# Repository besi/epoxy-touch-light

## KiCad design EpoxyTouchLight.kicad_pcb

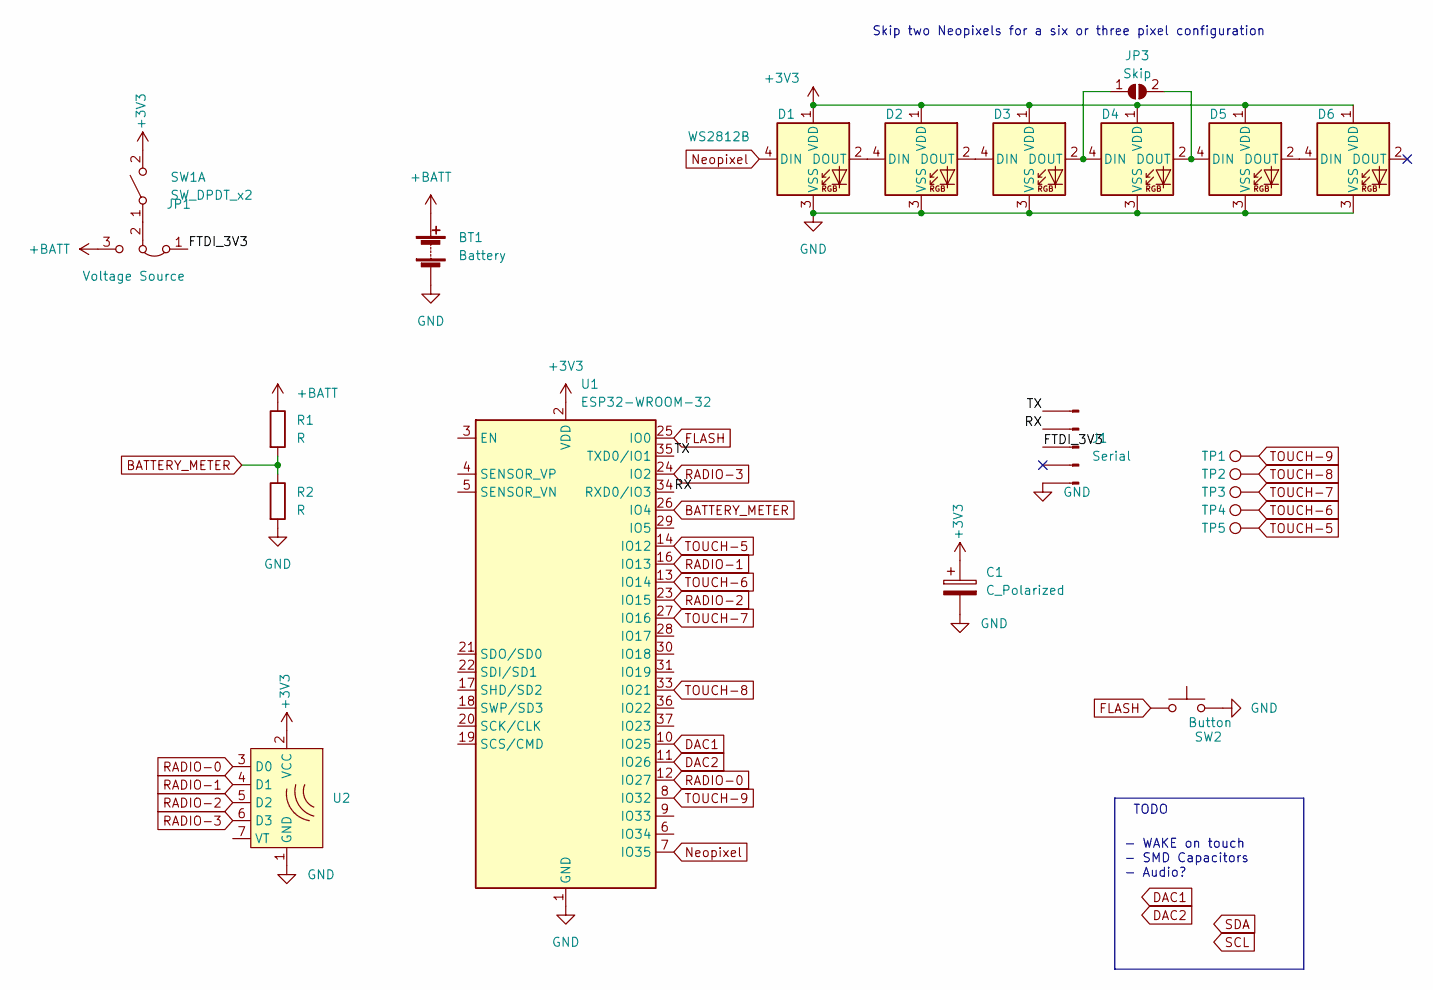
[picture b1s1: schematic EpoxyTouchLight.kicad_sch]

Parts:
BT1: Battery; BatteryHolder_Keystone_2479_3xAAA
C1: C_Polarized; CP_Radial_D5.0mm_P2.50mm
D1, D2, D3, D4, D5, D6: WS2812B; LED_WS2812B_PLCC4_5.0x5.0mm_P3.2mm
J1: Serial; PinHeader_1x05_P2.54mm_Horizontal
JP1: Voltage Source; PinHeader_1x03_P2.54mm_Horizontal
JP3: Skip; SolderJumper-2_P1.3mm_Open_TrianglePad1.0x1.5mm
R1, R2: R; R_Axial_DIN0207_L6.3mm_D2.5mm_P7.62mm_Horizontal
SW1: SW_DPDT_x2; SW_SPDT_CK-JS102011SAQN
SW2: Button; SW_PUSH_6mm_H4.3mm
TP1, TP2, TP3, TP4, TP5: Touch; TestPoint_Loop_D1.80mm_Drill1.0mm_Beaded
U1: ESP32-WROOM-32
U2: radio-receiver

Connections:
+3V3: C1.1, D1.1 (VDD), D2.1 (VDD), D3.1 (VDD), D4.1 (VDD), D5.1 (VDD), D6.1 (VDD), SW1.2 (B), U1.2 (VDD), U2.2 (VCC)
+BATT: BT1.1 (+), JP1.3 (B), R1.1
/FTDI_3V3: J1.3, JP1.1 (A)
/RX: J1.4, U1.34 (RXD0/IO3)
/TX: J1.5, U1.35 (TXD0/IO1)
BATTERY_METER: R1.2, R2.1, U1.26 (IO4)
DAC1: U1.10 (IO25)
DAC2: U1.11 (IO26)
FLASH: SW2.1, U1.25 (IO0)
GND: BT1.2 (-), C1.2, D1.3 (VSS), D2.3 (VSS), D3.3 (VSS), D4.3 (VSS), D5.3 (VSS), D6.3 (VSS), J1.1, R2.2, SW2.2, U1.1 (GND), U1.15 (GND), U1.38 (GND), U1.39 (GND), U2.1 (GND)
Neopixel: D1.4 (DIN), U1.7 (IO35)
unnamed: D1.2 (DOUT), D2.4 (DIN)
unnamed: D2.2 (DOUT), D3.4 (DIN)
unnamed: D3.2 (DOUT), D4.4 (DIN), JP3.1 (A)
unnamed: D4.2 (DOUT), D5.4 (DIN), JP3.2 (B)
unnamed: D5.2 (DOUT), D6.4 (DIN)
unnamed: JP1.2 (C), SW1.1 (A)
RADIO-0: U1.12 (IO27), U2.3 (D0)
RADIO-1: U1.16 (IO13), U2.4 (D1)
RADIO-2: U1.23 (IO15), U2.5 (D2)
RADIO-3: U1.24 (IO2), U2.6 (D3)
TOUCH-5: TP5.1, U1.14 (IO12)
TOUCH-6: TP4.1, U1.13 (IO14)
TOUCH-7: TP3.1, U1.27 (IO16)
TOUCH-8: TP2.1, U1.33 (IO21)
TOUCH-9: TP1.1, U1.8 (IO32)

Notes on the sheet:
Skip two Neopixels for a six or three pixel configuration
TODO
- WAKE on touch - SMD Capacitors - Audio?

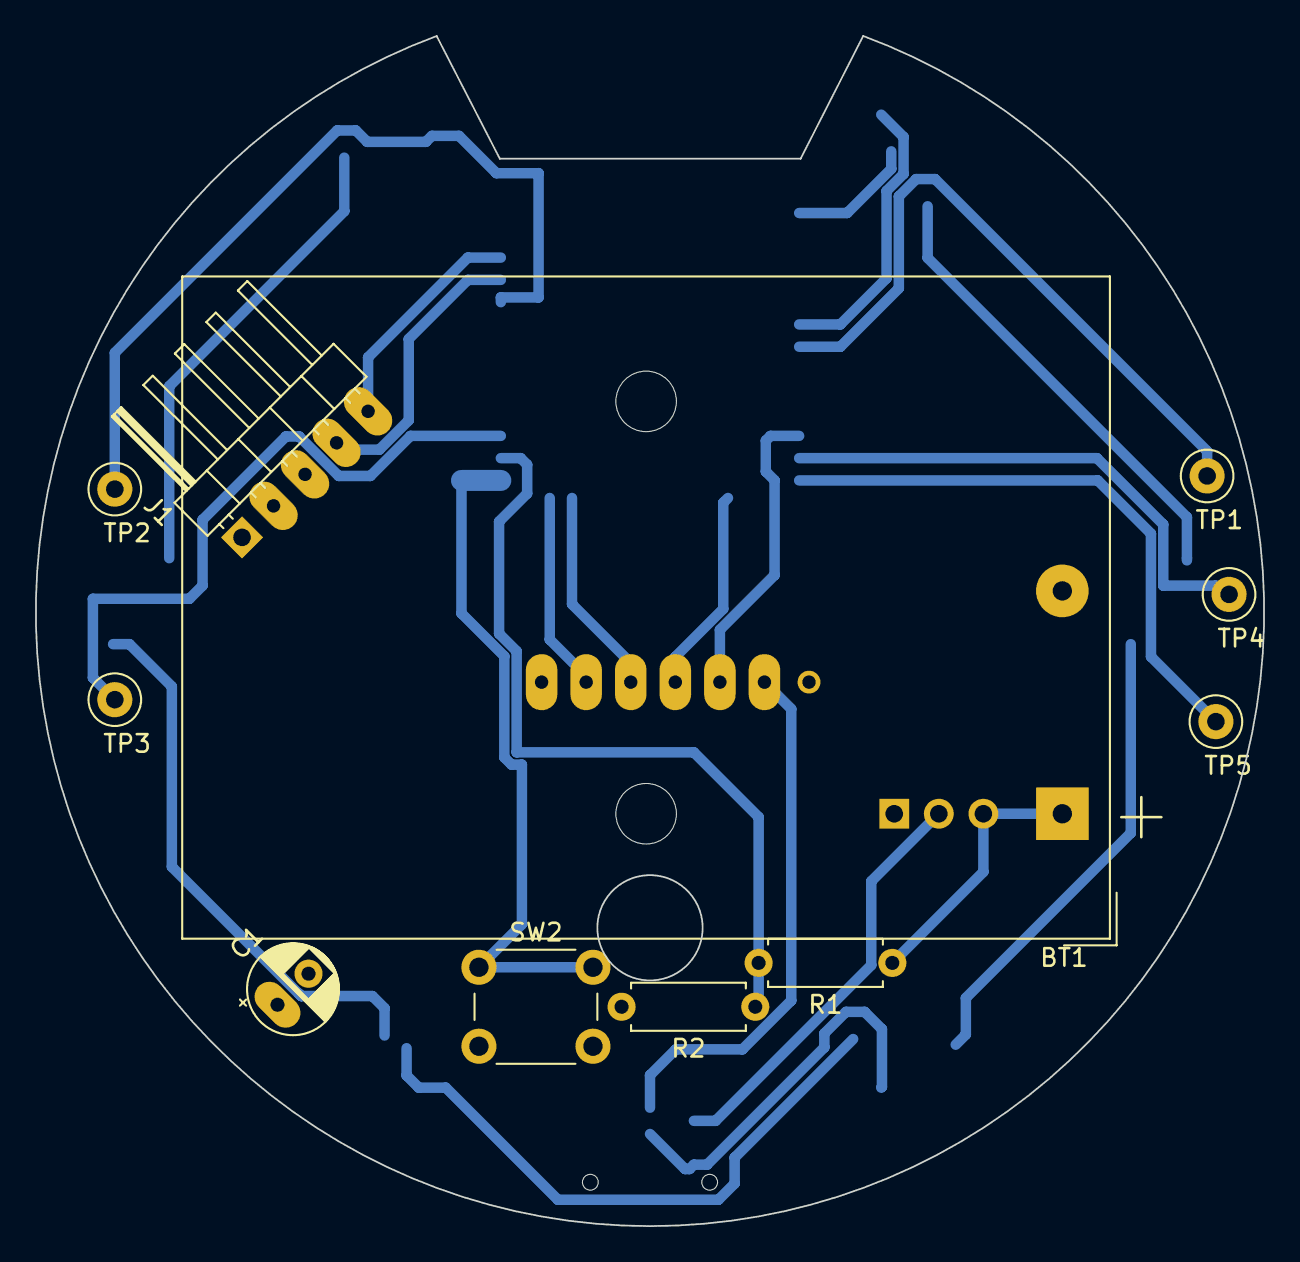
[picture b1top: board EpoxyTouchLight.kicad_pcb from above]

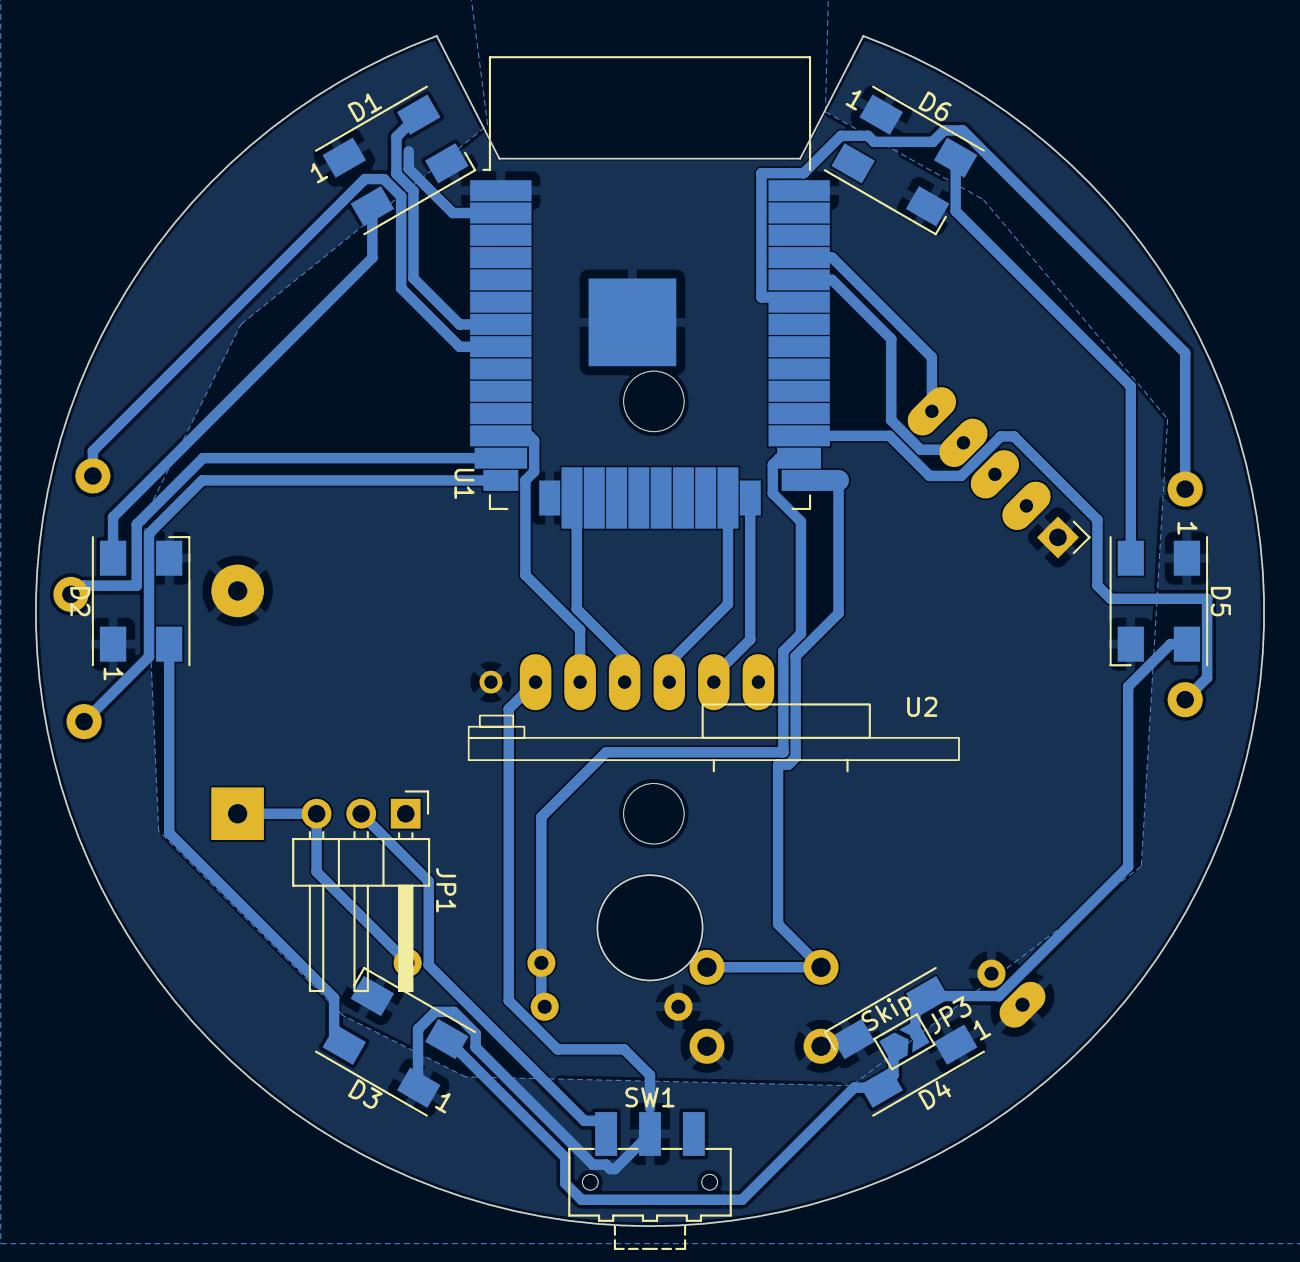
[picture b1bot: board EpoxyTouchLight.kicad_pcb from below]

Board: 2 copper layers, 70.0 x 67.8 mm, 22 parts (12 on the bottom side), 24 nets.

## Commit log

2022-12-25 Initial schematics and pcb
2022-12-26 Add radio receiver module
